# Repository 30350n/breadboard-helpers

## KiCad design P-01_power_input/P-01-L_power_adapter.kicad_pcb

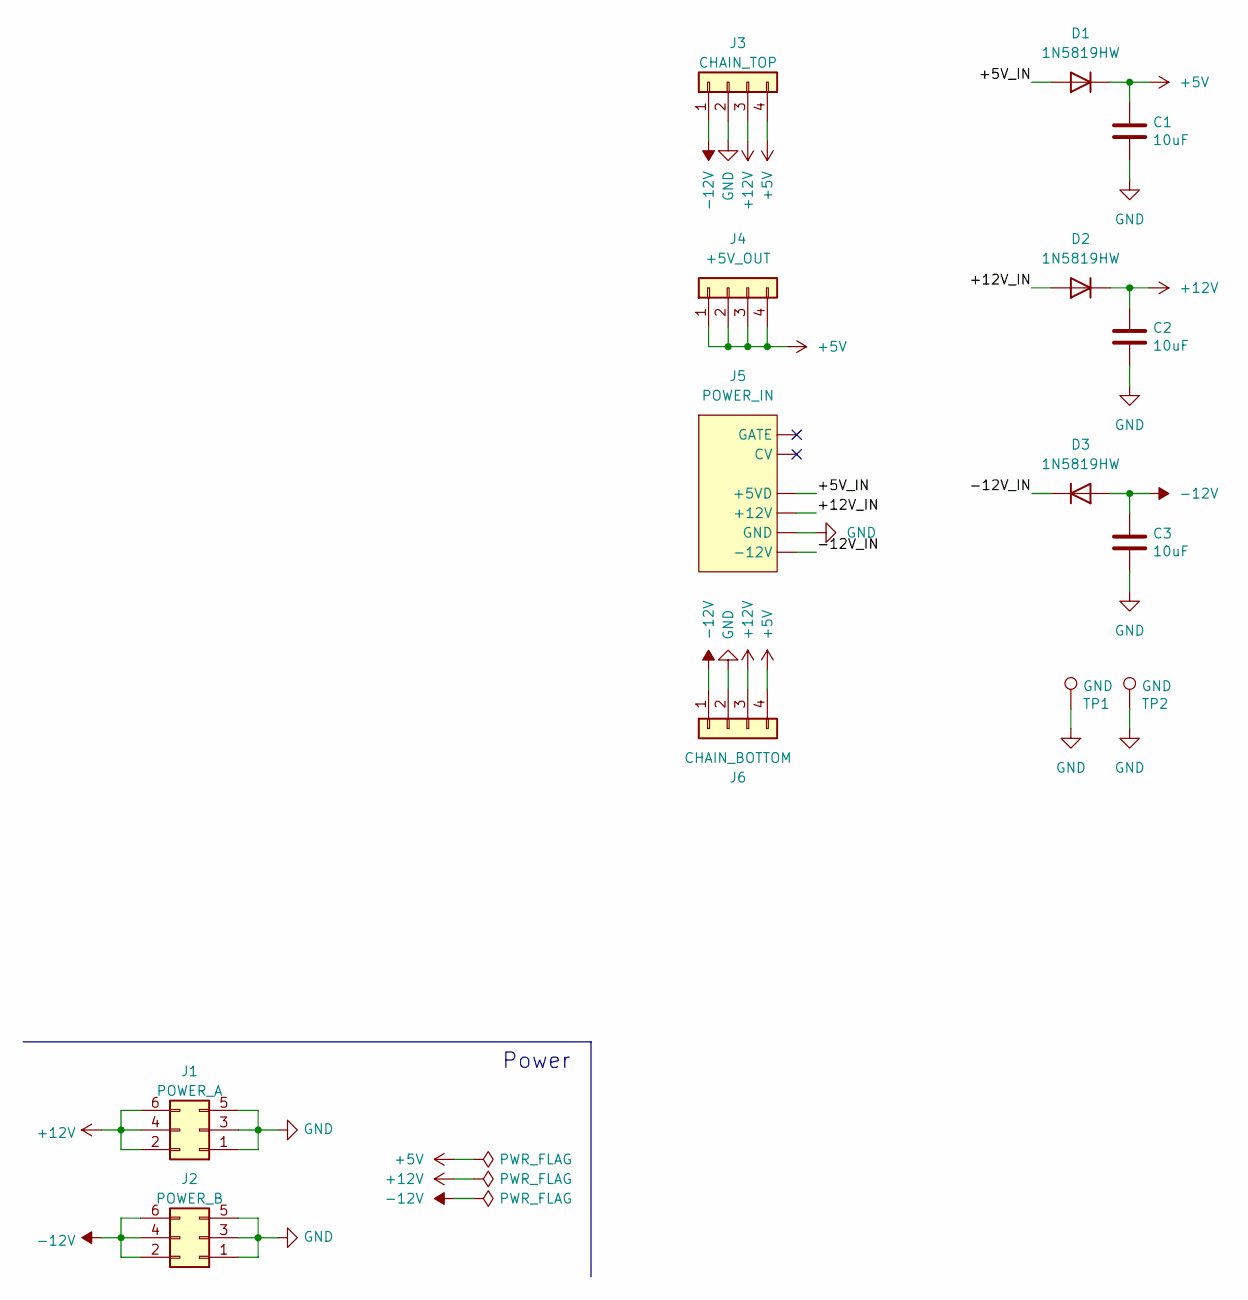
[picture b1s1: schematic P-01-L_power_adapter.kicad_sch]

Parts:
C1, C2, C3: 10uF; C_1206_3216Metric_Pad1.33x1.80mm_HandSolder
D1, D2, D3: 1N5819HW; D_SOD-123
J1: POWER_A; PinHeader_2x03_P2.54mm_Vertical
J2: POWER_B; PinHeader_2x03_P2.54mm_Vertical
J3: CHAIN_TOP; PinHeader_1x04_P2.54mm_Horizontal
J4: +5V_OUT; PinSocket_1x04_P2.54mm_Vertical
J5: POWER_IN; Eurorack_Power_Header_2x08_THT
J6: CHAIN_BOTTOM; PinSocket_1x04_P2.54mm_Horizontal
TP1, TP2: GND; TestPoint_THTPad_D1.5mm_Drill0.7mm

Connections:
+5V: C1.1, D1.1 (K), J3.4, J4.1, J4.2, J4.3, J4.4, J6.4
+12V: C2.1, D2.1 (K), J1.2, J1.4, J1.6, J3.3, J6.3
-12V: C3.1, D3.2 (A), J2.2, J2.4, J2.6, J3.1, J6.1
/+5V_IN: D1.2 (A), J5.+5VD
/+12V_IN: D2.2 (A), J5.+12V
/-12V_IN: D3.1 (K), J5.-12V
GND: C1.2, C2.2, C3.2, J1.1, J1.3, J1.5, J2.1, J2.3, J2.5, J3.2, J5.GND, J6.2, TP1.1, TP2.1

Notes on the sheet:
Power

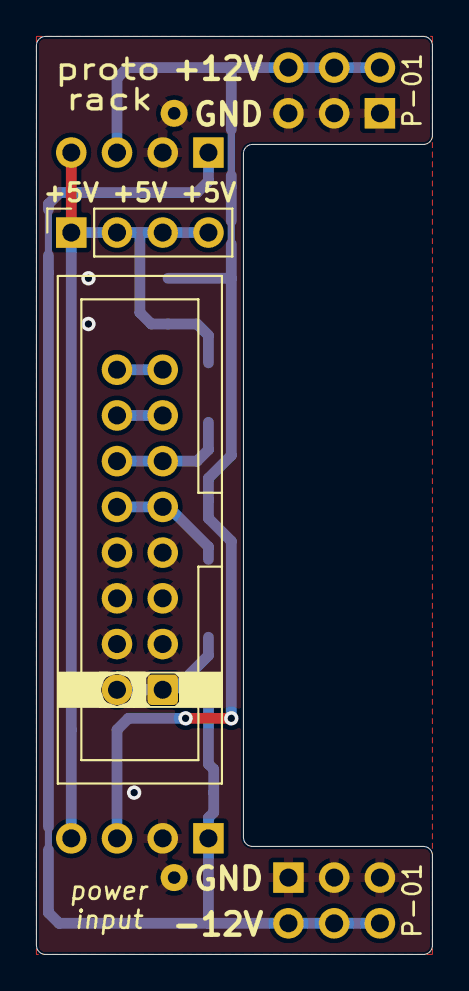
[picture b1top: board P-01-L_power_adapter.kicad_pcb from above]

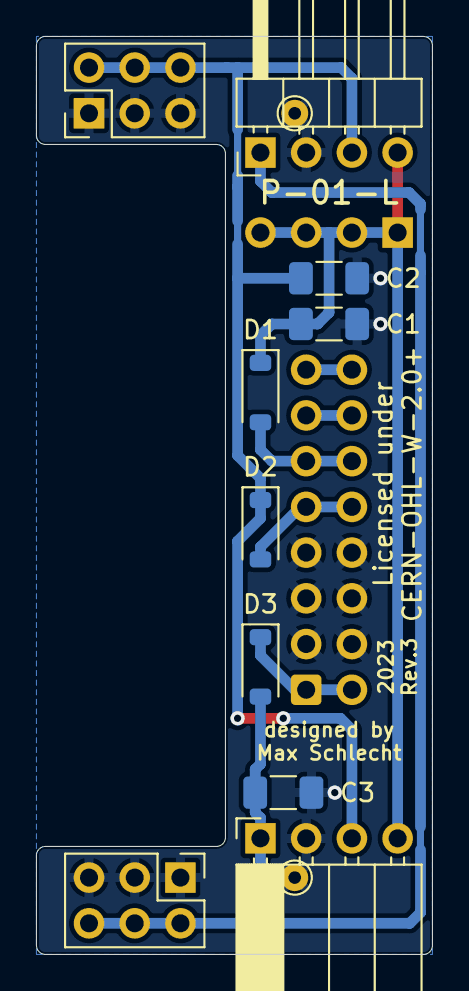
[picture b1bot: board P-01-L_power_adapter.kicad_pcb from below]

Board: 2 copper layers, 22.0 x 51.0 mm, 14 parts (12 on the bottom side), 7 nets.

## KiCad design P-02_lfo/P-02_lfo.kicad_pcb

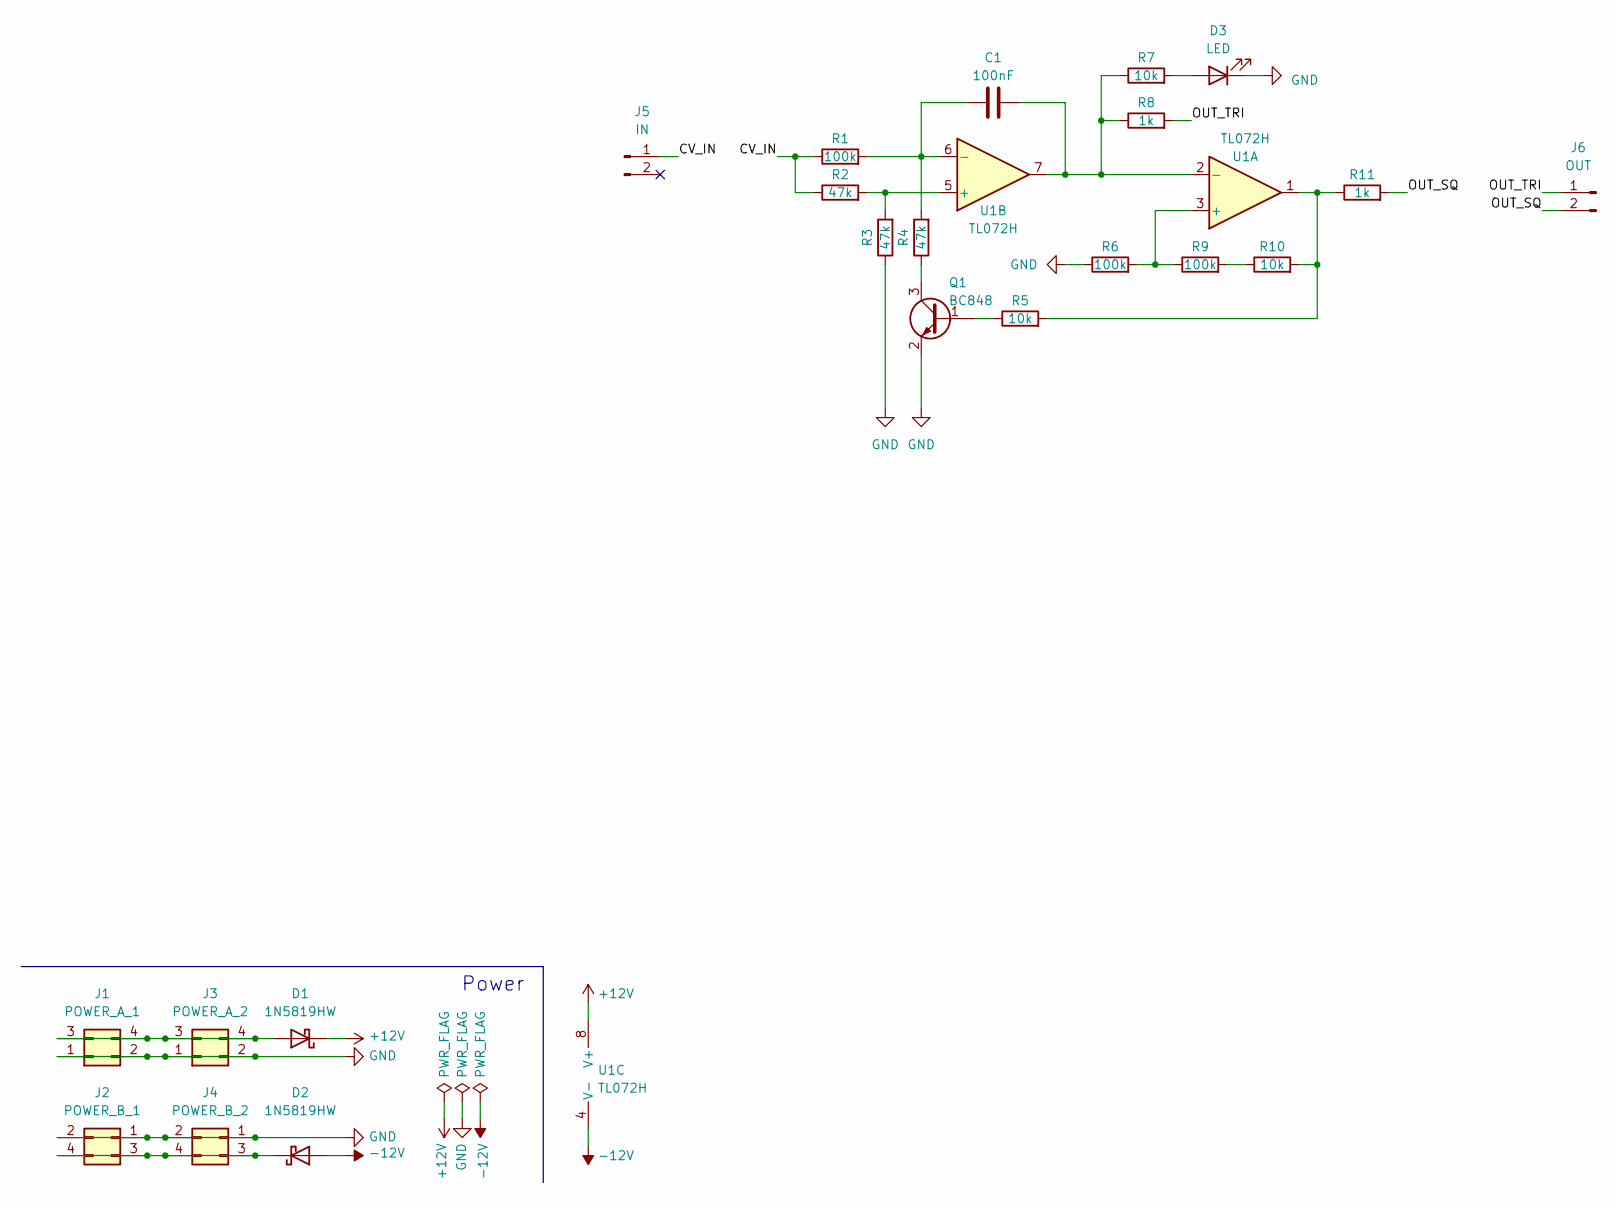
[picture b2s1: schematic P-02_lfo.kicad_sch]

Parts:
C1: 100nF; C_0805_2012Metric_Pad1.18x1.45mm_HandSolder
D1, D2: 1N5819HW; D_SOD-123
D3: LED; LED_1206_3216Metric_Pad1.42x1.75mm_HandSolder
J1: POWER_A_1; PinHeader_2x02_P2.54mm_Vertical
J2: POWER_B_1; PinHeader_2x02_P2.54mm_Vertical
J3: POWER_A_2; PinHeader_2x02_P2.54mm_Vertical
J4: POWER_B_2; PinHeader_2x02_P2.54mm_Vertical
J5: IN; PinHeader_1x02_P2.54mm_Vertical
J6: OUT; PinHeader_1x02_P2.54mm_Vertical
Q1: BC848; SOT-23_Handsoldering
R1, R6, R9: 100k; R_0805_2012Metric_Pad1.20x1.40mm_HandSolder
R2, R3, R4: 47k; R_0805_2012Metric_Pad1.20x1.40mm_HandSolder
R5, R7, R10: 10k; R_0805_2012Metric_Pad1.20x1.40mm_HandSolder
R8, R11: 1k; R_0805_2012Metric_Pad1.20x1.40mm_HandSolder
U1: TL072H; SOIC-8_3.9x4.9mm_P1.27mm

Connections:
+12V: D1.1 (K), U1.8 (V+)
-12V: D2.2 (A), U1.4 (V-)
/CV_IN: J5.1, R1.1, R2.1
/OUT_SQ: J6.2, R11.2
/OUT_TRI: J6.1, R8.2
GND: D3.1 (K), J1.1, J1.2, J2.1, J2.2, J3.1, J3.2, J4.1, J4.2, Q1.2 (E), R3.1, R6.1
unnamed: D1.2 (A), J1.3, J1.4, J3.3, J3.4
unnamed: D2.1 (K), J2.3, J2.4, J4.3, J4.4
unnamed: D3.2 (A), R7.2
unnamed: Q1.1 (B), R5.1
unnamed: Q1.3 (C), R4.1
unnamed: R9.2, R10.1
unnamed: R5.2, R10.2, R11.1, U1.1
unnamed: R6.2, R9.1, U1.3 (+)
unnamed: C1.2, R7.1, R8.1, U1.2 (-), U1.7
unnamed: R2.2, R3.2, U1.5 (+)
unnamed: C1.1, R1.2, R4.2, U1.6 (-)

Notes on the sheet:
Power

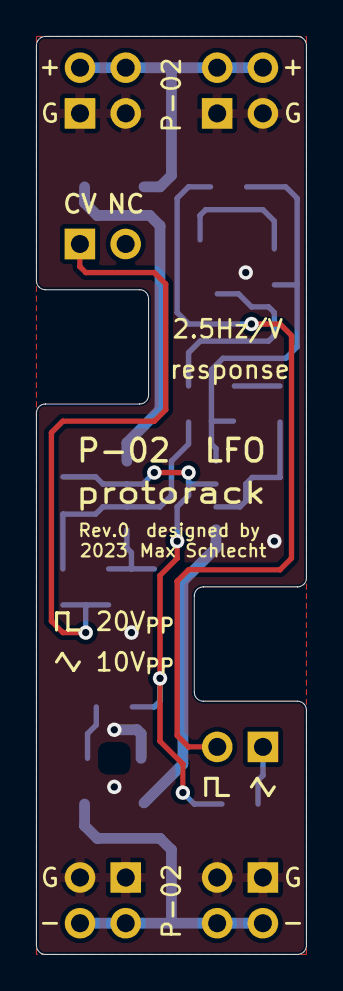
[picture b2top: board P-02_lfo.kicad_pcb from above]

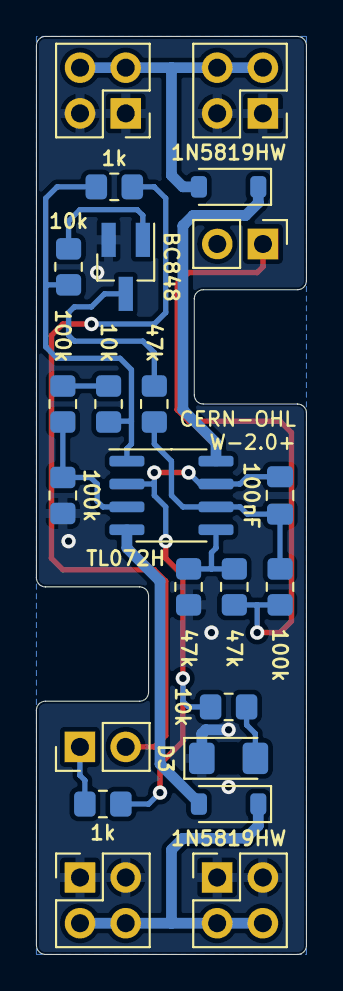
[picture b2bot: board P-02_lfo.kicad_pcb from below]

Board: 2 copper layers, 15.0 x 51.0 mm, 23 parts (23 on the bottom side), 17 nets.

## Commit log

2023-05-24 Initial commit, Add template submodule
2023-05-25 Update template, Add project library
2023-05-25 Add .gitignore
2023-05-25 Add P-01 power input
2023-05-25 Add P-02 lfo
2023-05-25 Set stackup colors, copper finish
2023-05-26 Fix P-01 file associations, diodes, erc check
2023-05-26 Adjust plot settings

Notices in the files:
P-01_power_input/P-01-L_power_adapter.kicad_pcb:
Licensed under
CERN-OHL-W-2.0+
P-02_lfo/P-02_lfo.kicad_pcb:
CERN-OHL
